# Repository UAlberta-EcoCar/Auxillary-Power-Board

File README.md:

# Auxillary-Power-Board
Files for the Auxillary Power Board

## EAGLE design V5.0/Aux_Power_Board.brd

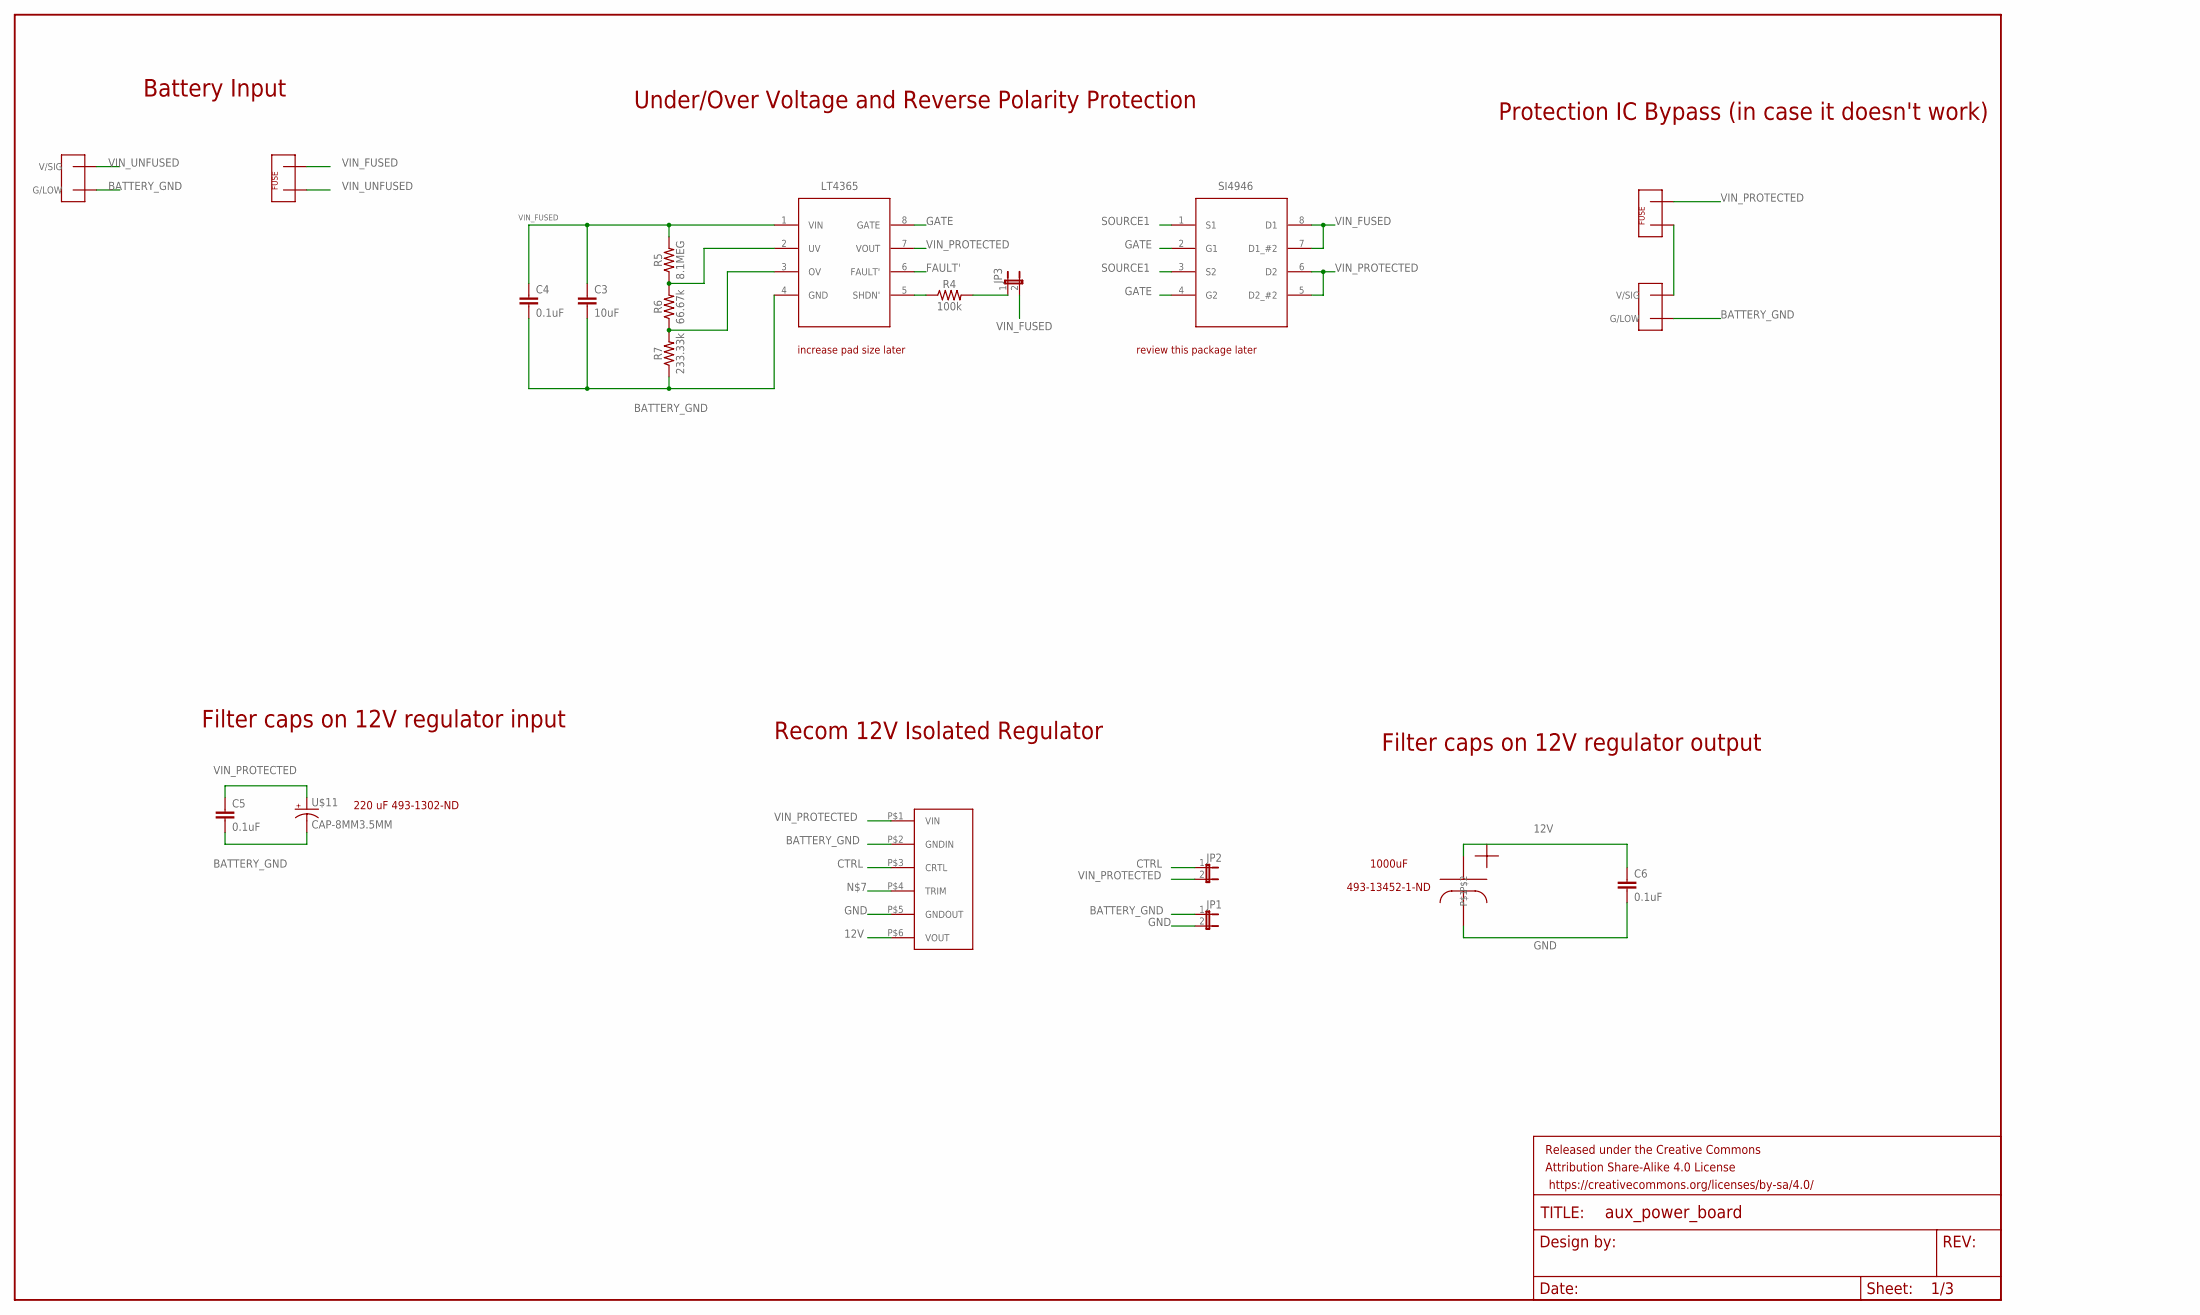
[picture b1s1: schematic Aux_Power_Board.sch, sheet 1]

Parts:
C3: 10uF; 0805
C4, C5, C6: 0.1uF; 0805
FRAME2: FRAME-LEDGER; CREATIVE_COMMONS
JP1, JP2, JP3: JP1E; JP1
R4: 100k; 0805
R5: 8.1MEG; 0805
R6: 66.67k; 0805
R7: 233.33k; 0805
U$5: LT4365; TSOT-23_TS8
U$6: SI4946; SOIC127P600X175-8N
U$11: CAP-8MM3.5MM; CAP-8MM*3.5MM
U$12: RPA60-2412SFW_P; RPA60-2412SFW/P
U$13, U$20: FUSEMINI-BLADE; MINI-BLADE-FUSE
U$14, U$21: TE770966; 2X1-MATE-N-LOCK
U$22: CAPESK108M025AH4EA; ESK108M025AH4EA

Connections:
12V: C6.1, U$12.P$6 (VOUT), U$22.P$1; also elsewhere on the board
BATTERY_GND: C3.2, C4.2, C5.2, JP1.1, R7.1, U$5.4 (GND), U$11.P$2 (-), U$12.P$2 (GNDIN), U$14.CIRCUIT2 (G/LOW), U$21.CIRCUIT2 (G/LOW); also elsewhere on the board
CTRL: JP2.1, U$12.P$3 (CRTL)
FAULT': U$5.6 (FAULT'); also elsewhere on the board
GATE: U$5.8 (GATE), U$6.2 (G1), U$6.4 (G2)
GND: C6.2, JP1.2, U$12.P$5 (GNDOUT), U$22.P$2; also elsewhere on the board
unnamed: R4.1, U$5.5 (SHDN')
unnamed: R5.1, R6.2, U$5.2 (UV)
unnamed: R6.1, R7.2, U$5.3 (OV)
unnamed: JP3.1, R4.2
unnamed: U$20.IN, U$21.CIRCUIT1 (V/SIG)
SOURCE1: U$6.1 (S1), U$6.3 (S2)
VIN_FUSED: C3.1, C4.1, JP3.2, R5.2, U$5.1 (VIN), U$6.7 (D1_#2), U$6.8 (D1), U$13.OUT; also elsewhere on the board
VIN_PROTECTED: C5.1, JP2.2, U$5.7 (VOUT), U$6.5 (D2_#2), U$6.6 (D2), U$11.P$1 (+), U$12.P$1 (VIN), U$20.OUT; also elsewhere on the board
VIN_UNFUSED: U$13.IN, U$14.CIRCUIT1 (V/SIG)

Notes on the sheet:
Battery Input
Under/Over Voltage and Reverse Polarity Protection
220 uF 493-1302-ND
Filter caps on 12V regulator input
increase pad size later
Protection IC Bypass (in case it doesn't work)
review this package later
Filter caps on 12V regulator output
Recom 12V Isolated Regulator
1000uF
493-13452-1-ND

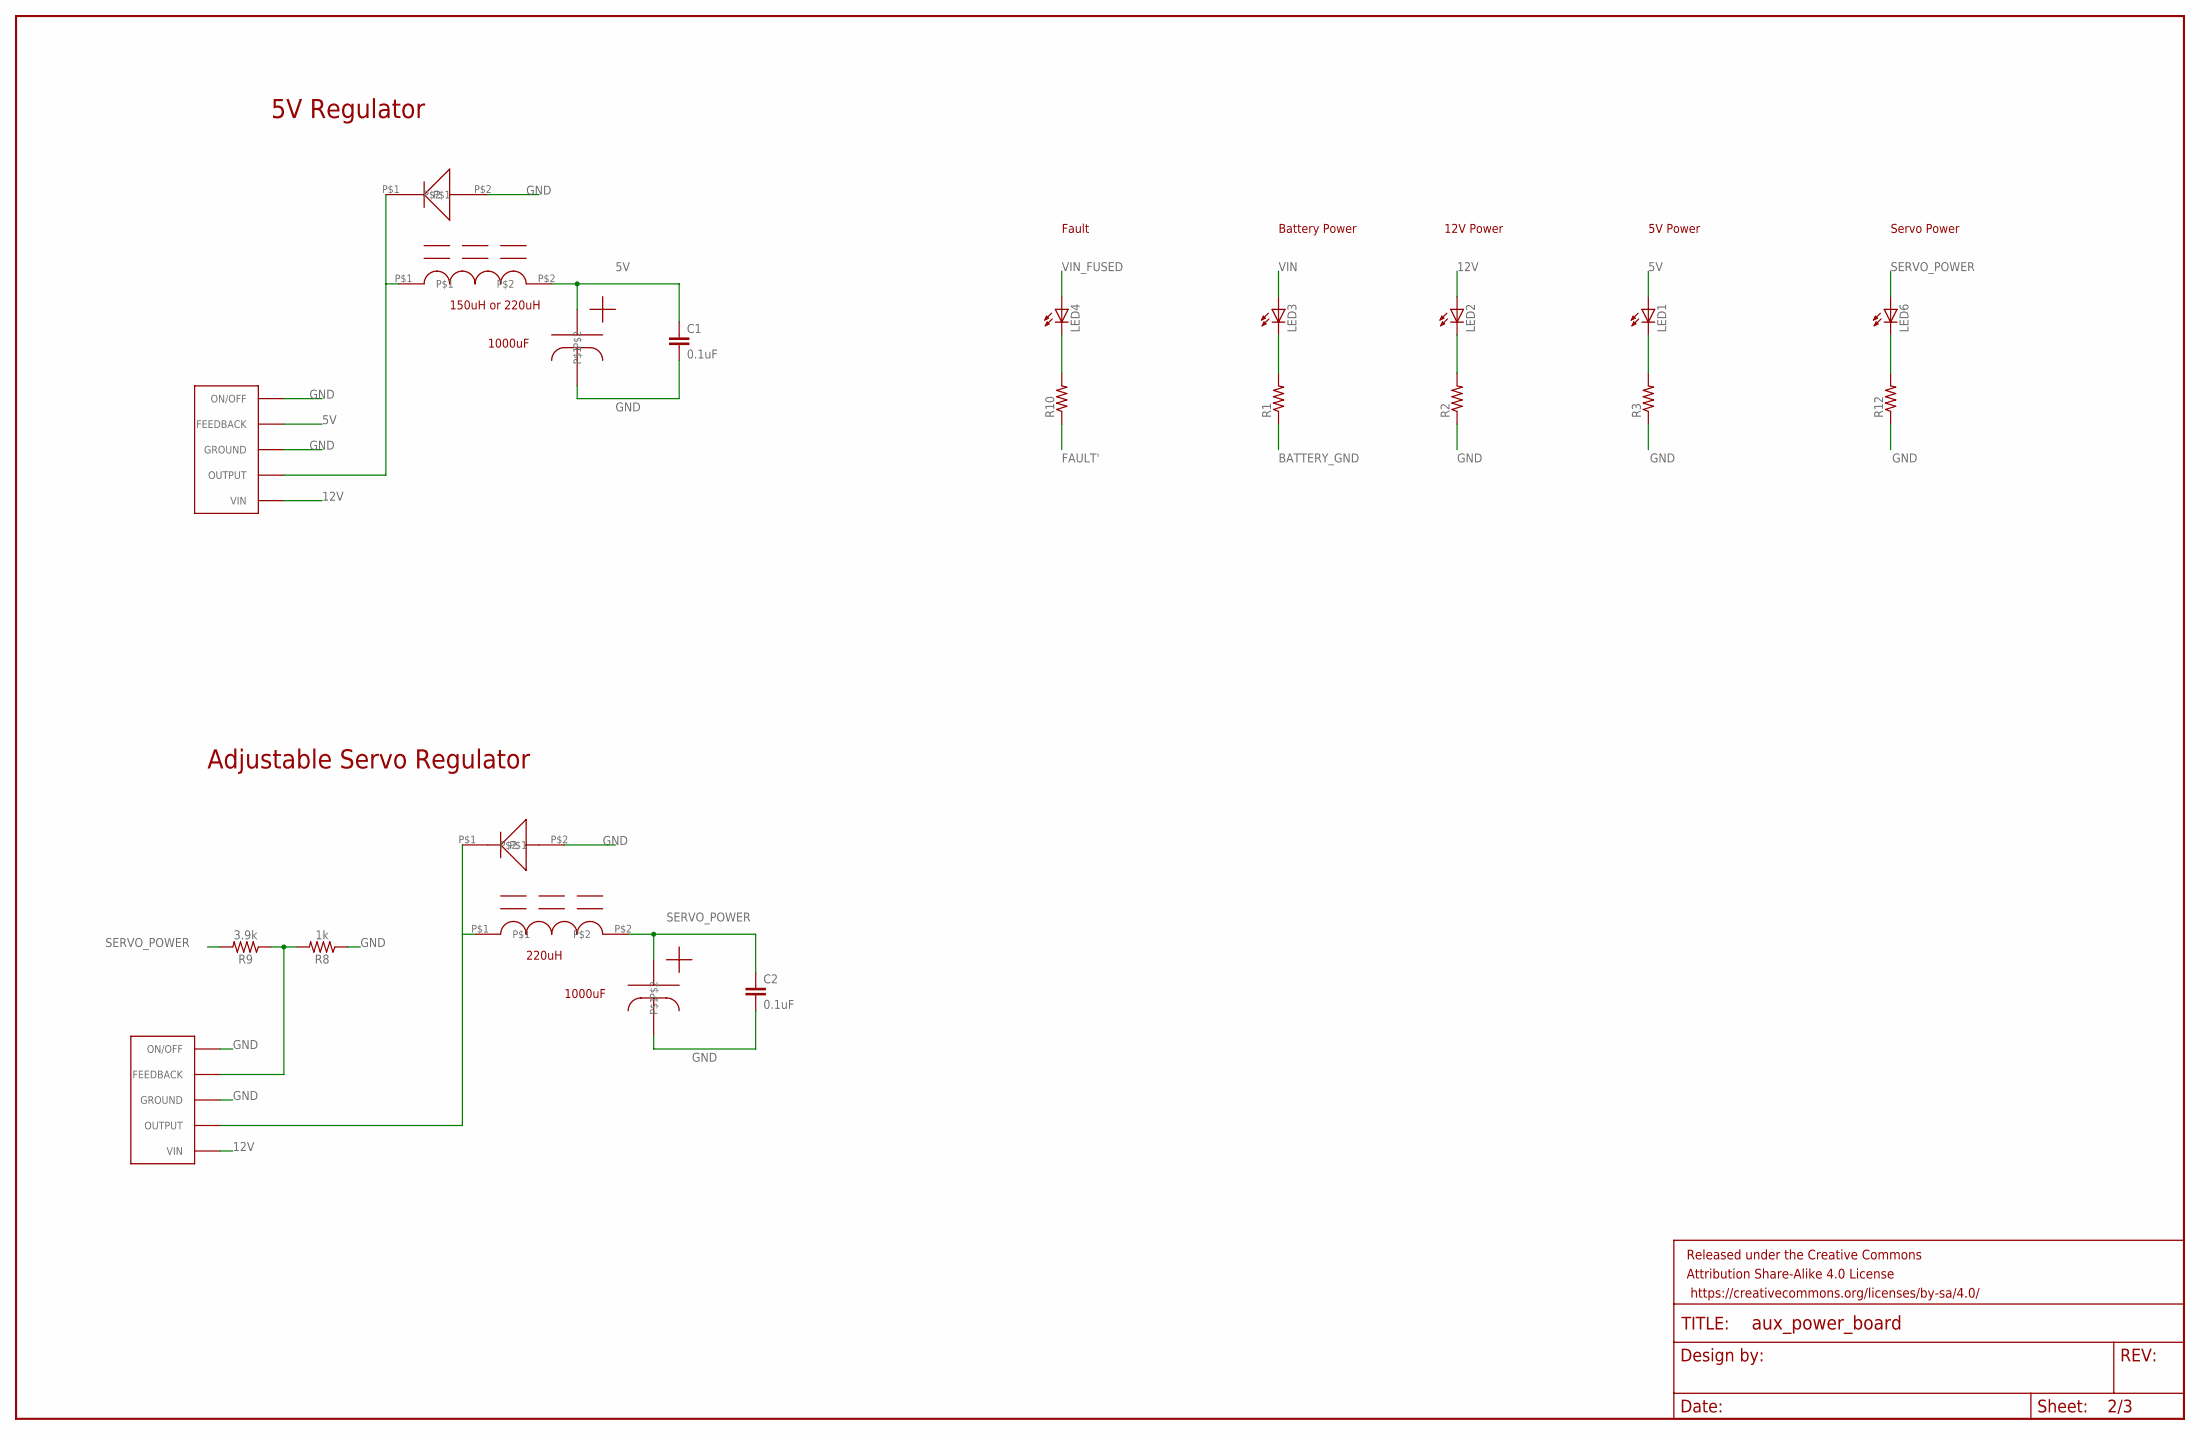
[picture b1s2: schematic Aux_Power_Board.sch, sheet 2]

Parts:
C1, C2: 0.1uF; 0805
FRAME1: FRAME-LEDGER; CREATIVE_COMMONS
LED1, LED2, LED3, LED4, LED6: LEDCHIP-LED0805; CHIP-LED0805
R1, R2, R3, R10, R12: R-US_M0805; M0805
R8: 1k; 0805
R9: 3.9k; 0805
U$4, U$8: MBR360GOS
U$7, U$23: LM2576; D2PAK-5
U$9, U$24: CAPESK108M025AH4EA; ESK108M025AH4EA
U$10, U$25: M1418-ND

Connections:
5V: C1.1, LED1.A, U$7.4 (FEEDBACK), U$9.P$1, U$10.P$2; also elsewhere on the board
12V: LED2.A, U$7.1 (VIN), U$23.1 (VIN); also elsewhere on the board
BATTERY_GND: R1.1; also elsewhere on the board
FAULT': R10.1; also elsewhere on the board
GND: C1.2, C2.2, R2.1, R3.1, R8.1, R12.1, U$4.P$2, U$7.3 (GROUND), U$7.5 (ON/OFF), U$7.GROUND, U$8.P$2, U$9.P$2, U$23.3 (GROUND), U$23.5 (ON/OFF), U$23.GROUND, U$24.P$2; also elsewhere on the board
unnamed: U$4.P$1, U$7.2 (OUTPUT), U$10.P$1
unnamed: LED3.C, R1.2
unnamed: LED2.C, R2.2
unnamed: LED1.C, R3.2
unnamed: U$8.P$1, U$23.2 (OUTPUT), U$25.P$1
unnamed: R8.2, R9.1, U$23.4 (FEEDBACK)
unnamed: LED4.C, R10.2
unnamed: LED6.C, R12.2
SERVO_POWER: C2.1, LED6.A, R9.2, U$24.P$1, U$25.P$2; also elsewhere on the board
VIN: LED3.A
VIN_FUSED: LED4.A; also elsewhere on the board

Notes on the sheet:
1000uF
5V Regulator
Adjustable Servo Regulator
Fault
Battery Power
12V Power
5V Power
Servo Power
220uH
150uH or 220uH

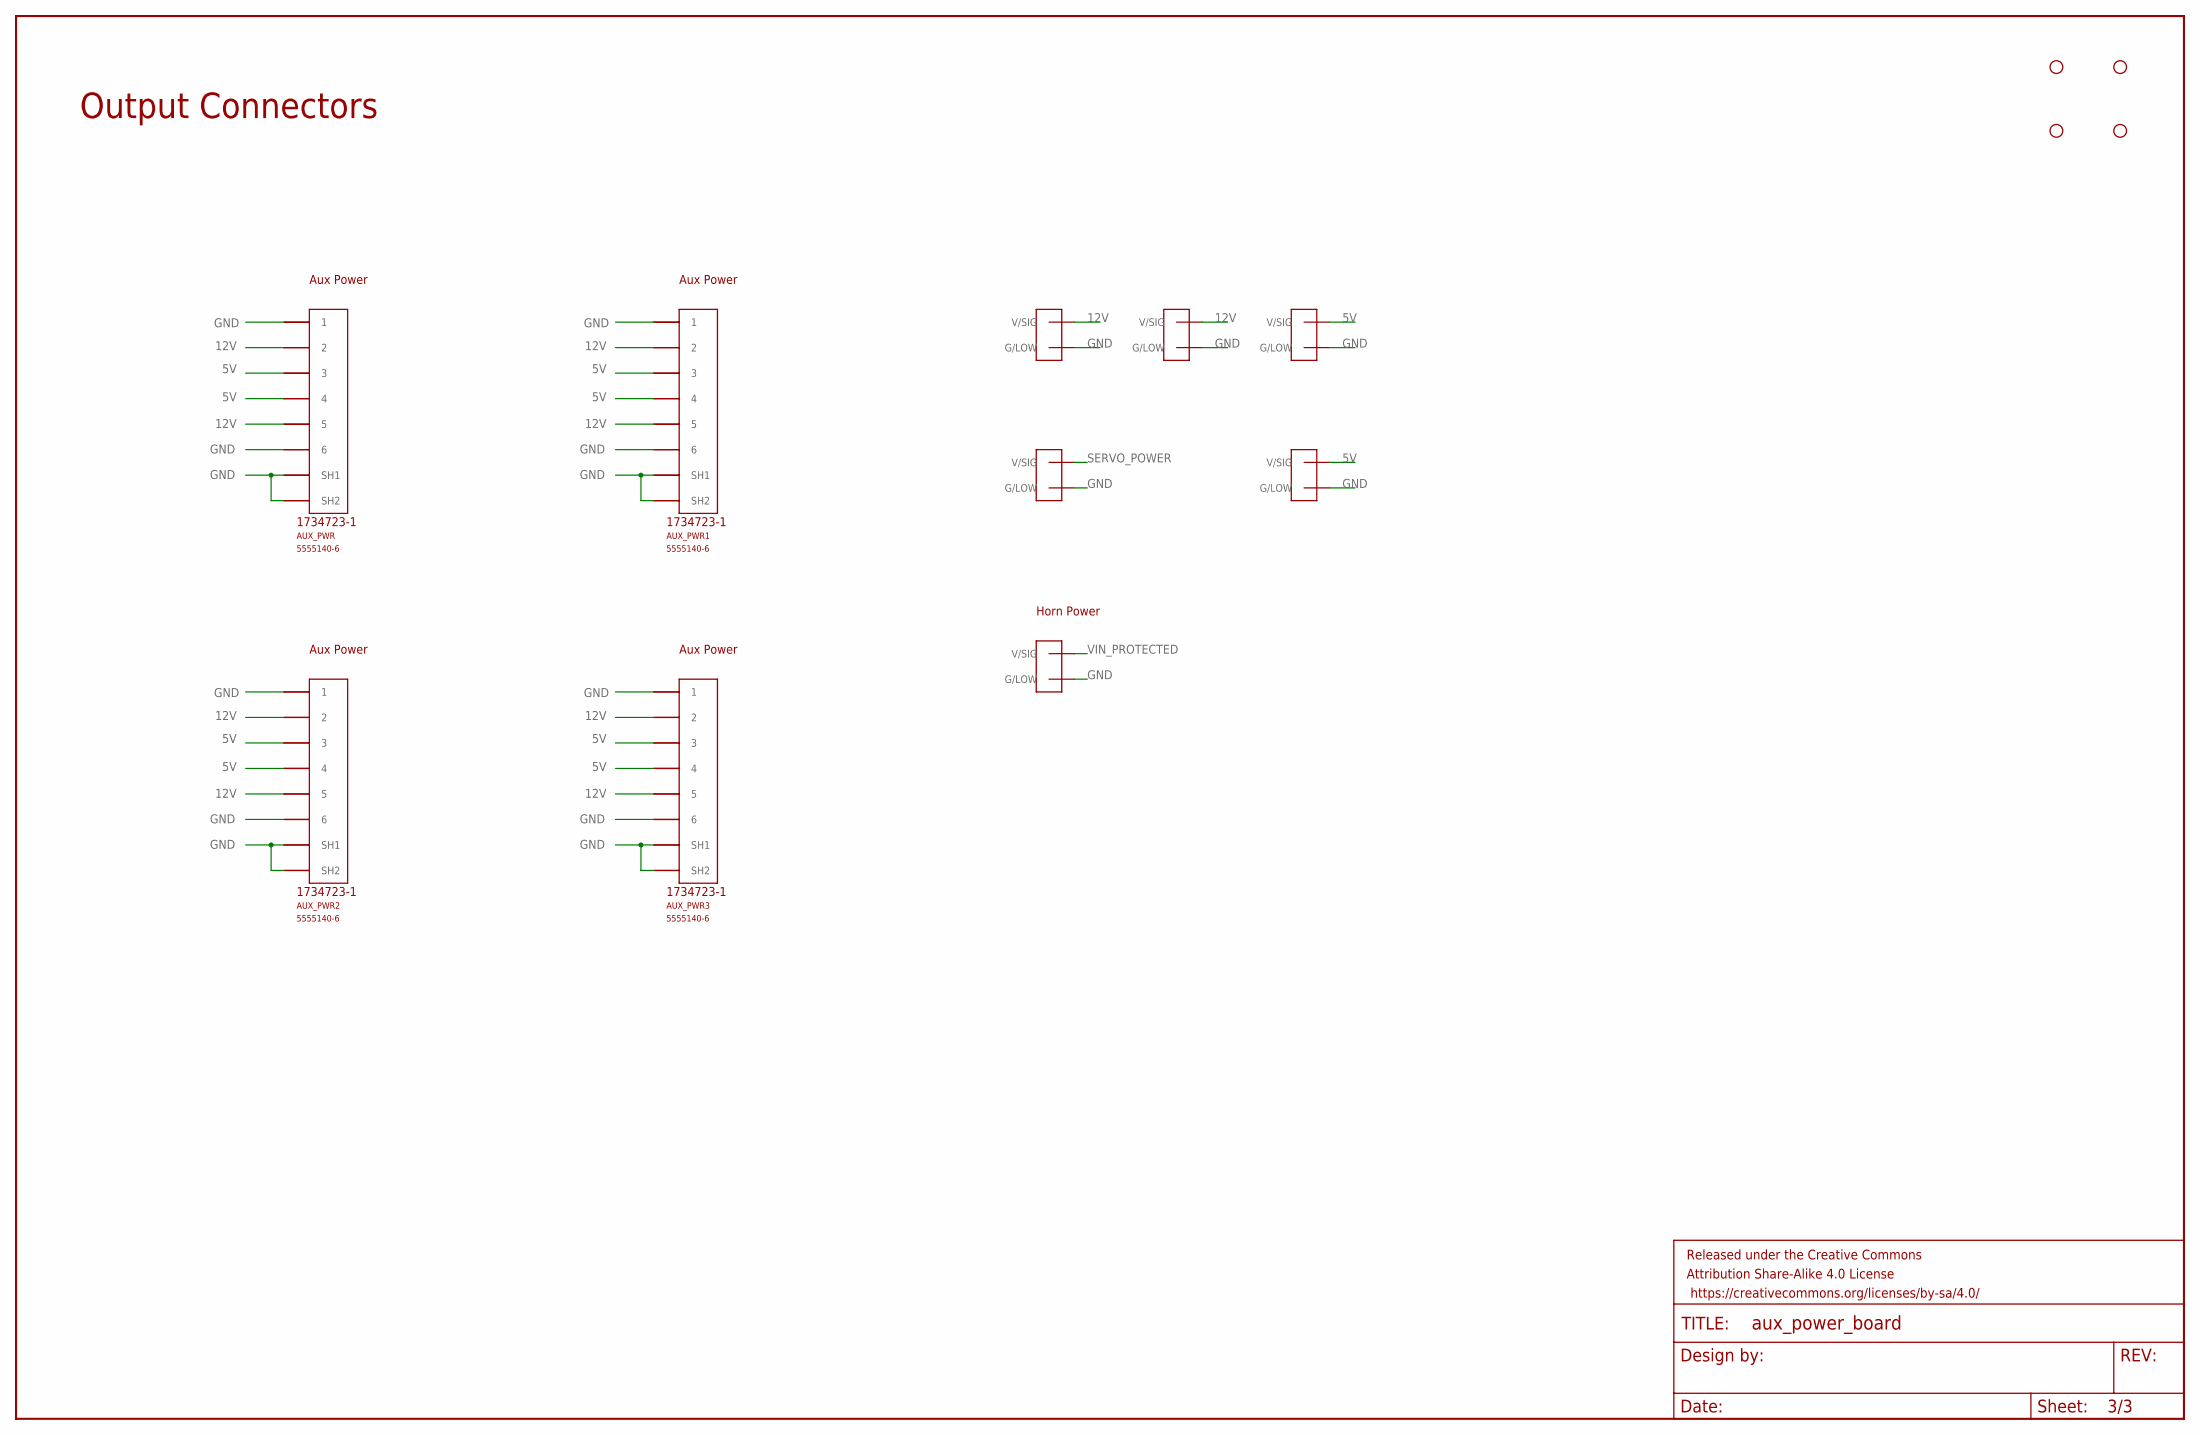
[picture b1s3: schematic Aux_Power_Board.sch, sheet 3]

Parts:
AUX_PWR, AUX_PWR1, AUX_PWR2, AUX_PWR3: 5555140-6; 1734723-1_RJ11
FRAME4: FRAME-LEDGER; CREATIVE_COMMONS
H1, H2, H3, H4: STAND-OFF
U$1, U$2, U$3, U$15, U$26, U$27: TE770966; 2X1-MATE-N-LOCK

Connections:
5V: AUX_PWR.3, AUX_PWR.4, AUX_PWR1.3, AUX_PWR1.4, AUX_PWR2.3, AUX_PWR2.4, AUX_PWR3.3, AUX_PWR3.4, U$3.CIRCUIT1 (V/SIG), U$27.CIRCUIT1 (V/SIG); also elsewhere on the board
12V: AUX_PWR.2, AUX_PWR.5, AUX_PWR1.2, AUX_PWR1.5, AUX_PWR2.2, AUX_PWR2.5, AUX_PWR3.2, AUX_PWR3.5, U$1.CIRCUIT1 (V/SIG), U$2.CIRCUIT1 (V/SIG); also elsewhere on the board
GND: AUX_PWR.1, AUX_PWR.6, AUX_PWR.SH1, AUX_PWR.SH2, AUX_PWR1.1, AUX_PWR1.6, AUX_PWR1.SH1, AUX_PWR1.SH2, AUX_PWR2.1, AUX_PWR2.6, AUX_PWR2.SH1, AUX_PWR2.SH2, AUX_PWR3.1, AUX_PWR3.6, AUX_PWR3.SH1, AUX_PWR3.SH2, U$1.CIRCUIT2 (G/LOW), U$2.CIRCUIT2 (G/LOW), U$3.CIRCUIT2 (G/LOW), U$15.CIRCUIT2 (G/LOW), U$26.CIRCUIT2 (G/LOW), U$27.CIRCUIT2 (G/LOW); also elsewhere on the board
SERVO_POWER: U$26.CIRCUIT1 (V/SIG); also elsewhere on the board
VIN_PROTECTED: U$15.CIRCUIT1 (V/SIG); also elsewhere on the board

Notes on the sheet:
Output Connectors
Aux Power
Horn Power

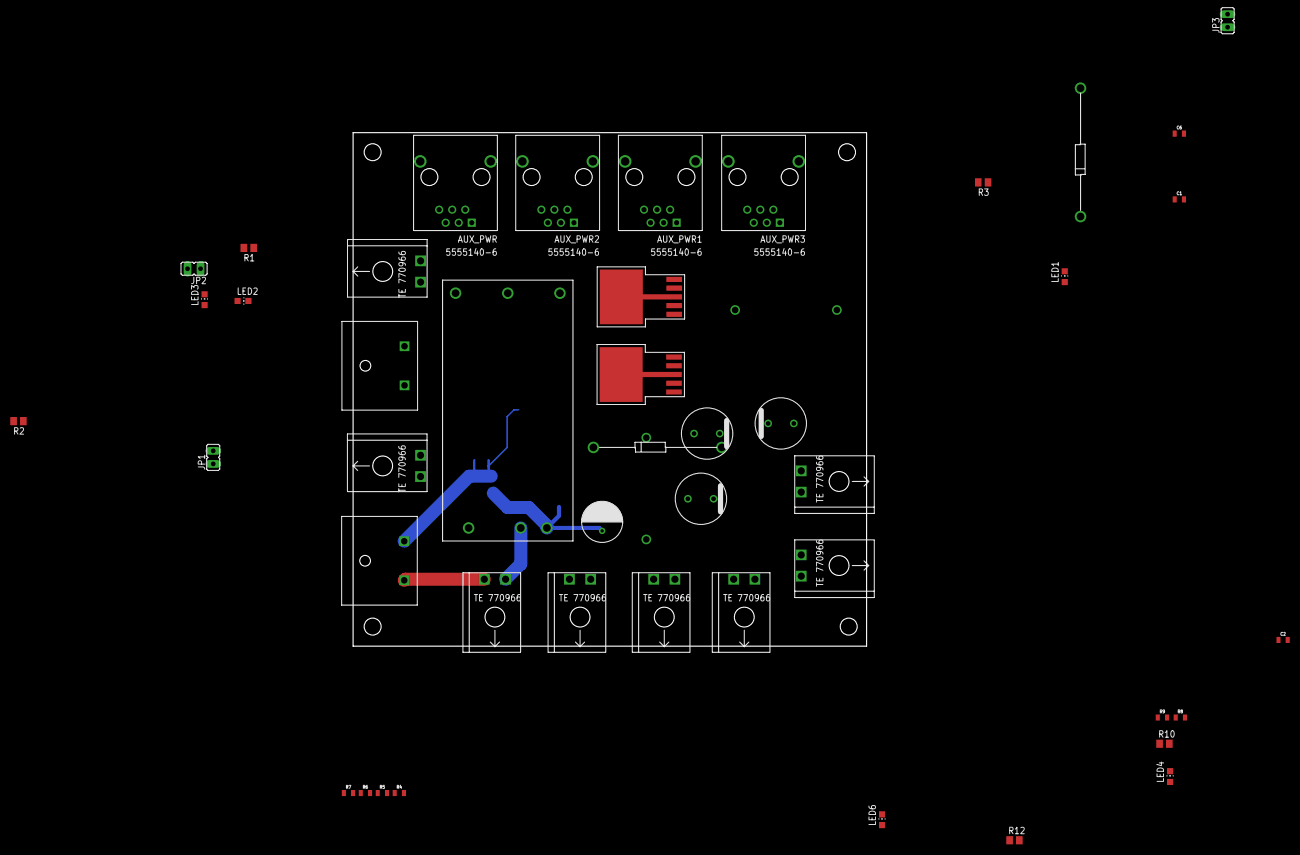
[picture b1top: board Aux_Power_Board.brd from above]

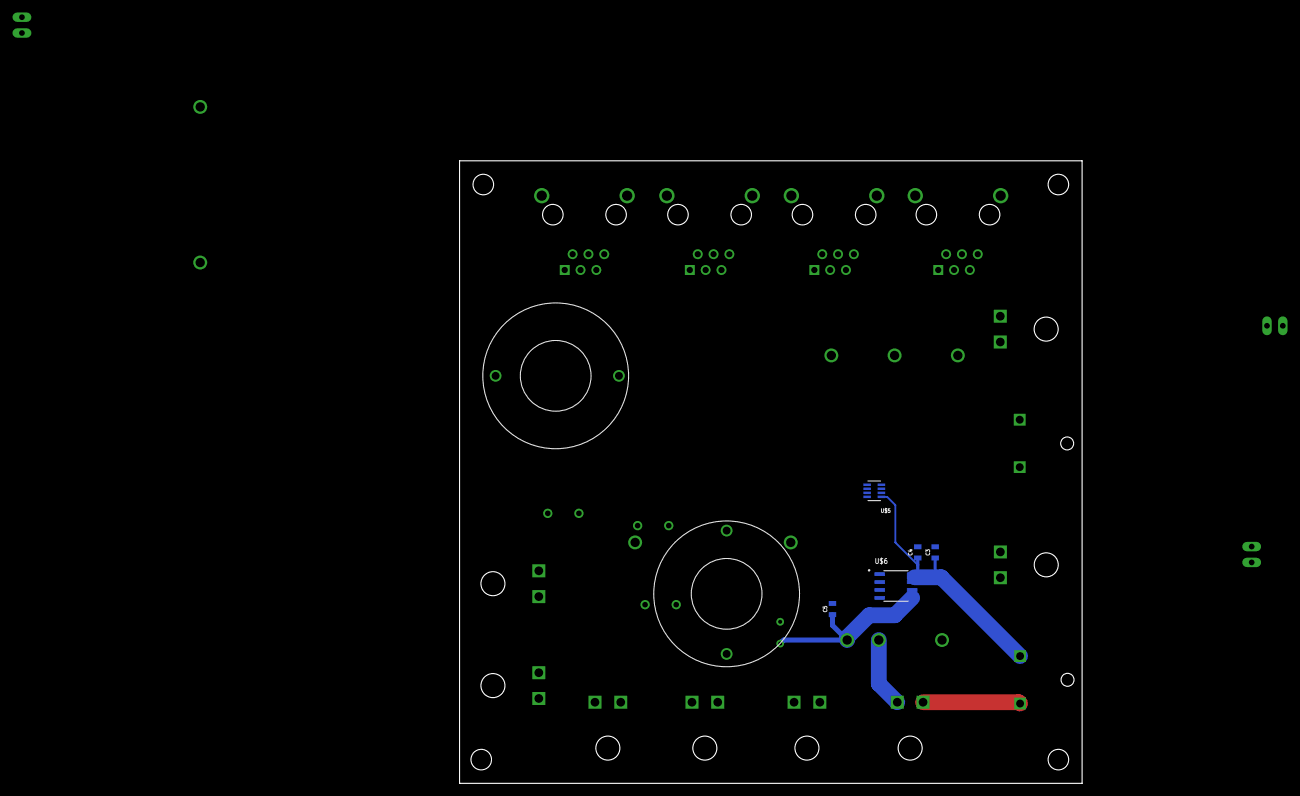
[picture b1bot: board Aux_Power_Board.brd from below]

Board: 2 copper layers, 100.0 x 100.0 mm, 59 parts (7 on the bottom side), 25 nets.

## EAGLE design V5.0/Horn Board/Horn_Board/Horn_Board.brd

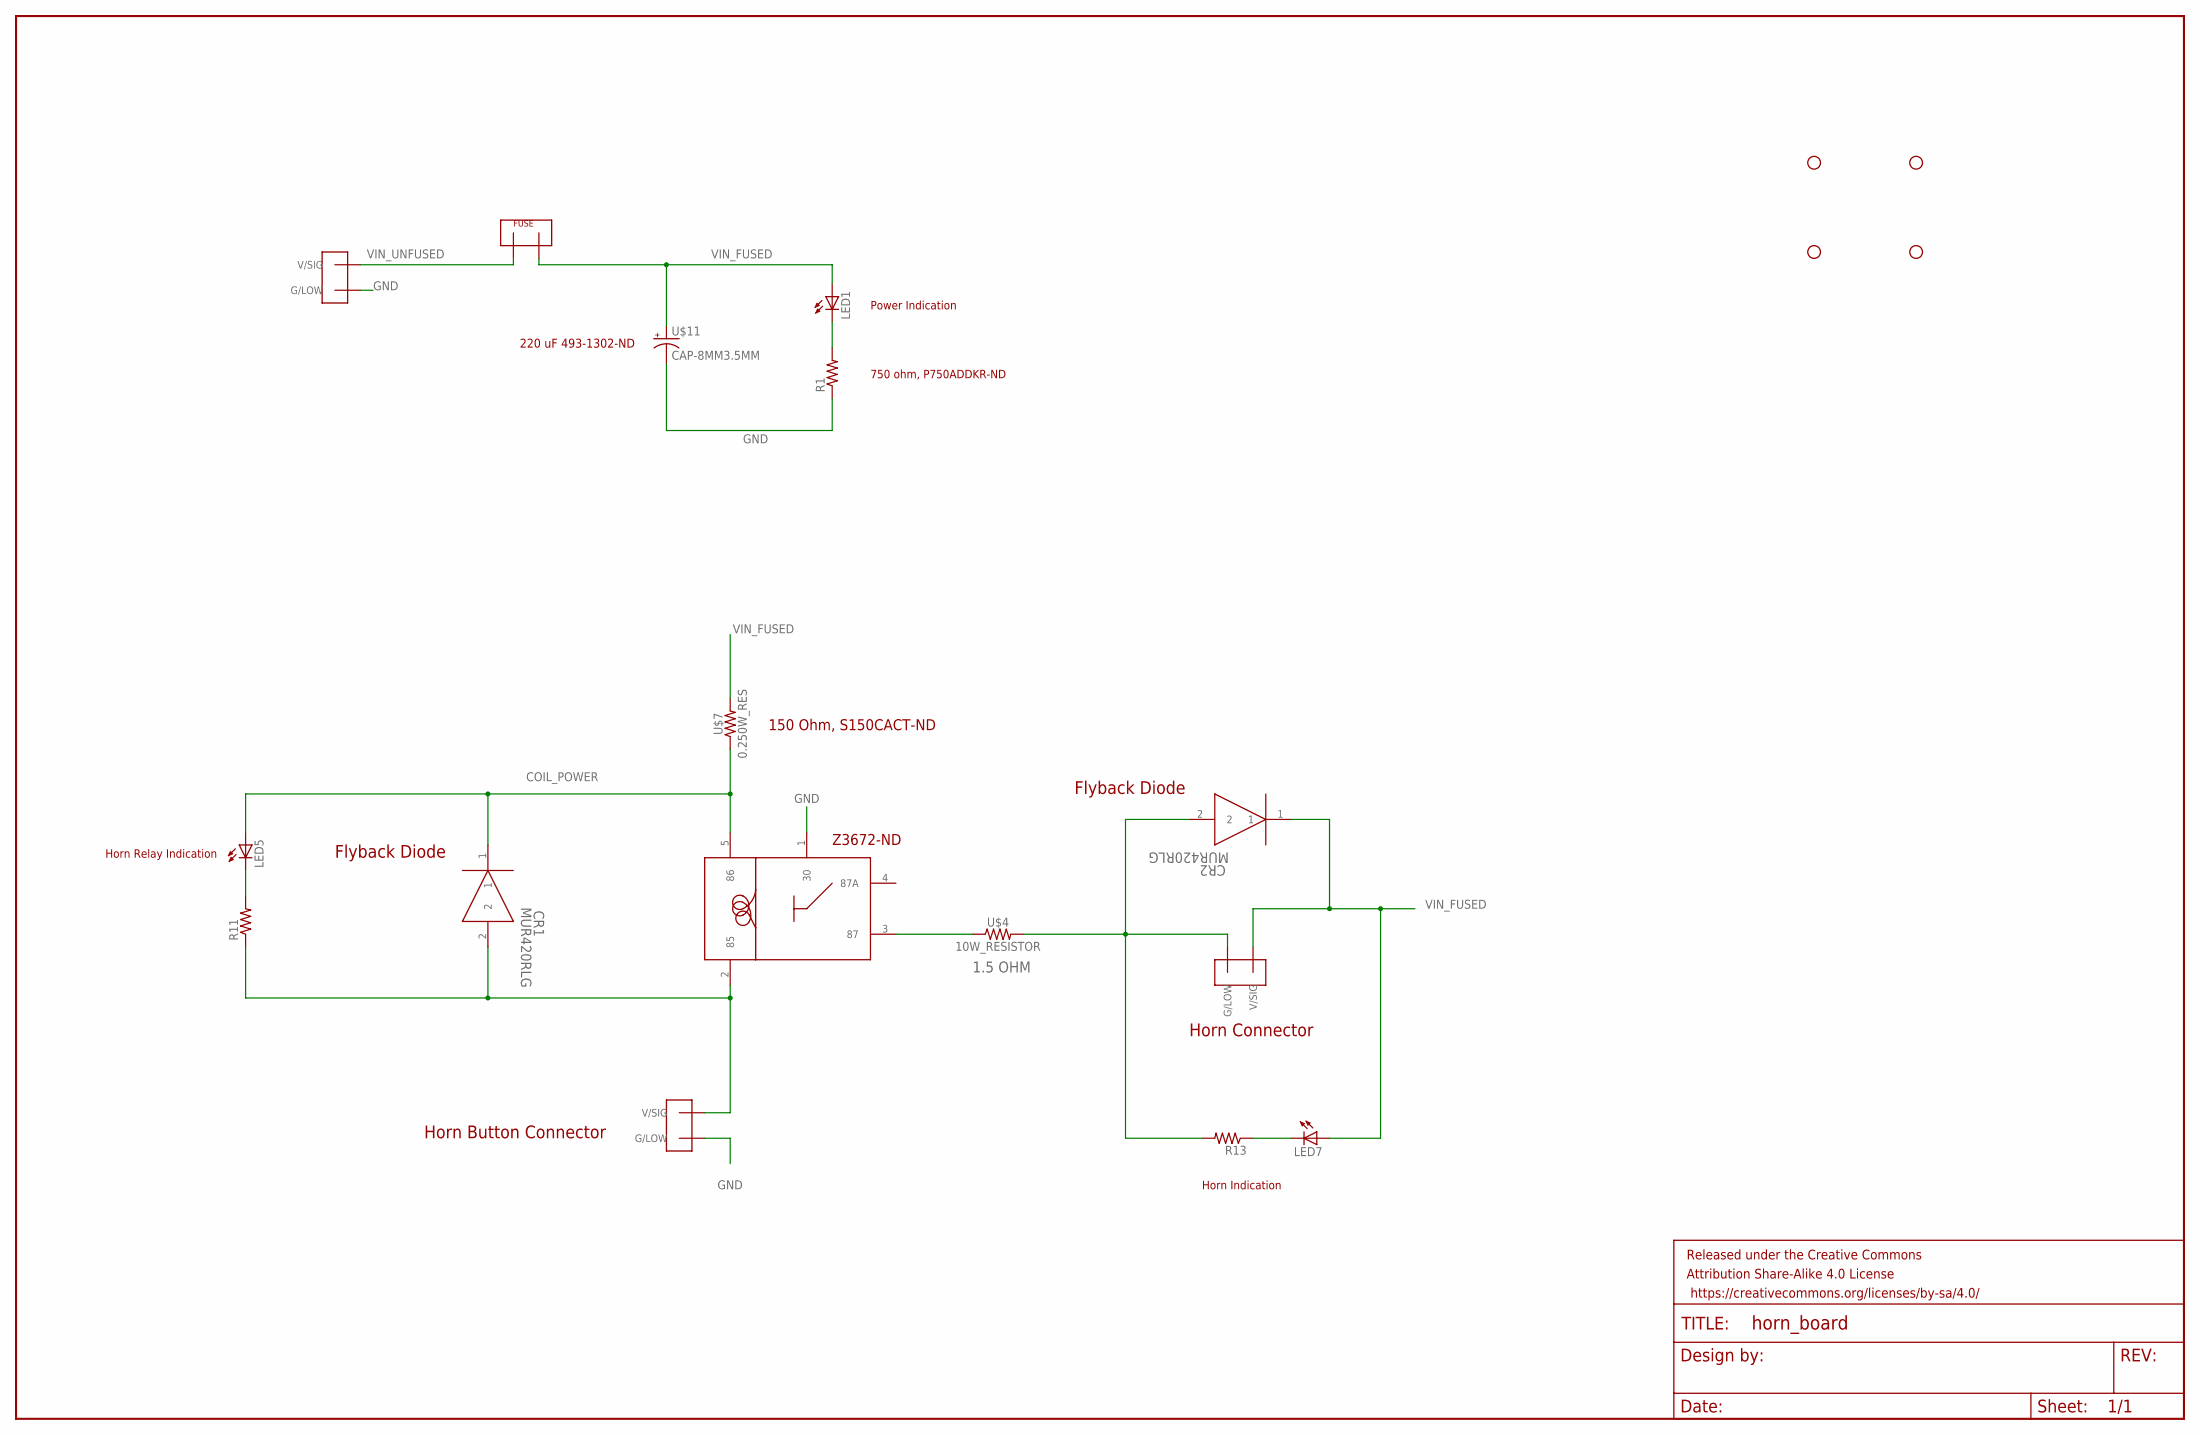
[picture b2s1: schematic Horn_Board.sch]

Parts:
CR1, CR2: MUR420RLG; DO-201AD
FRAME1: FRAME-LEDGER; CREATIVE_COMMONS
H1, H2, H3, H4: STAND-OFF
LED1, LED5, LED7: LEDCHIP-LED0805; CHIP-LED0805
R1, R11, R13: R-US_M0805; M0805
U$1, U$17, U$18: TE770966; 2X1-MATE-N-LOCK
U$2: FUSEMINI-BLADE; MINI-BLADE-FUSE
U$3: OMRON_G5LE-1
U$4: 10W_RESISTOR
U$7: 0.250W_RES; AXIAL-0.3
U$11: CAP-8MM3.5MM; CAP-8MM*3.5MM

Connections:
COIL_POWER: CR1.1, LED5.A, U$3.5 (86), U$7.P$1 (1)
GND: R1.1, U$1.CIRCUIT2 (G/LOW), U$3.1 (30), U$11.P$2 (-), U$17.CIRCUIT2 (G/LOW)
HORN-: CR2.2, R13.2, U$4.P$2 (2), U$18.CIRCUIT2 (G/LOW)
HORN_BUTTON: CR1.2, R11.1, U$3.2 (85), U$17.CIRCUIT1 (V/SIG)
unnamed: U$3.3 (87), U$4.P$1 (1)
unnamed: LED1.C, R1.2
unnamed: LED5.C, R11.2
unnamed: LED7.C, R13.1
VIN_FUSED: CR2.1, LED1.A, LED7.A, U$2.OUT, U$7.P$2 (2), U$11.P$1 (+), U$18.CIRCUIT1 (V/SIG)
VIN_UNFUSED: U$1.CIRCUIT1 (V/SIG), U$2.IN

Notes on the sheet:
1.5 OHM
Horn Connector
Flyback Diode
Horn Button Connector
220 uF 493-1302-ND
Z3672-ND
150 Ohm, S150CACT-ND
Horn Relay Indication
Horn Indication
Power Indication
750 ohm, P750ADDKR-ND

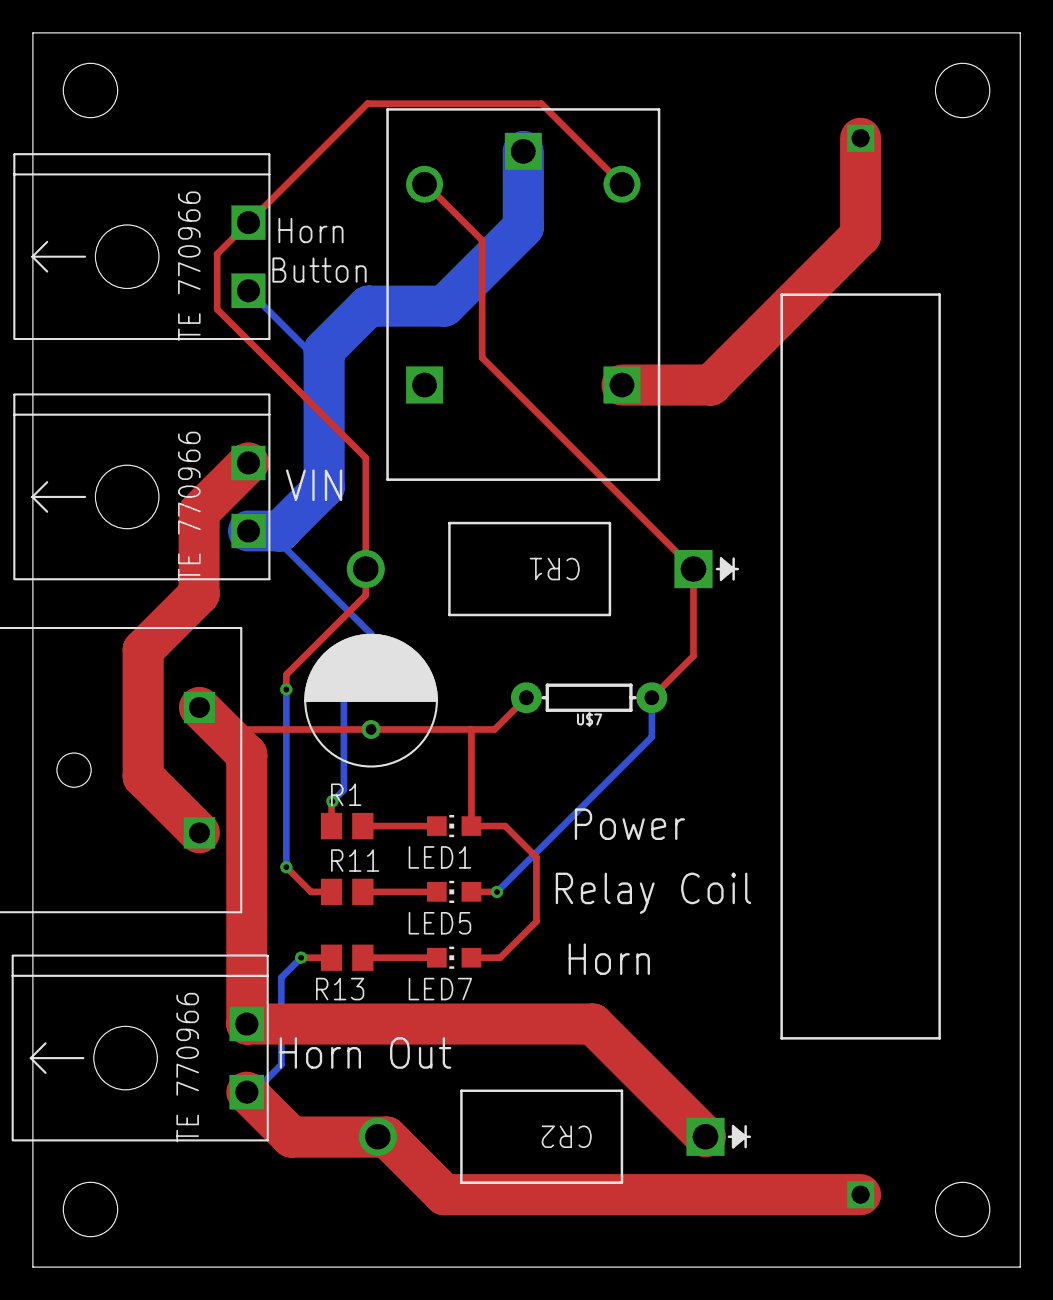
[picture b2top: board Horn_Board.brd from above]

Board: 2 copper layers, 60.0 x 75.0 mm, 21 parts (0 on the bottom side), 10 nets.

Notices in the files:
parts and their libraries:
SparkFun-Electromechanical: Licensing: Creative Commons ShareAlike 4.0 International - https://creativecommons.org/licenses/by-sa/4.0
SparkFun-Aesthetics: Released under the Creative Commons Attribution Share-Alike 4.0 License
SparkFun-Aesthetics: https://creativecommons.org/licenses/by-sa/4.0
